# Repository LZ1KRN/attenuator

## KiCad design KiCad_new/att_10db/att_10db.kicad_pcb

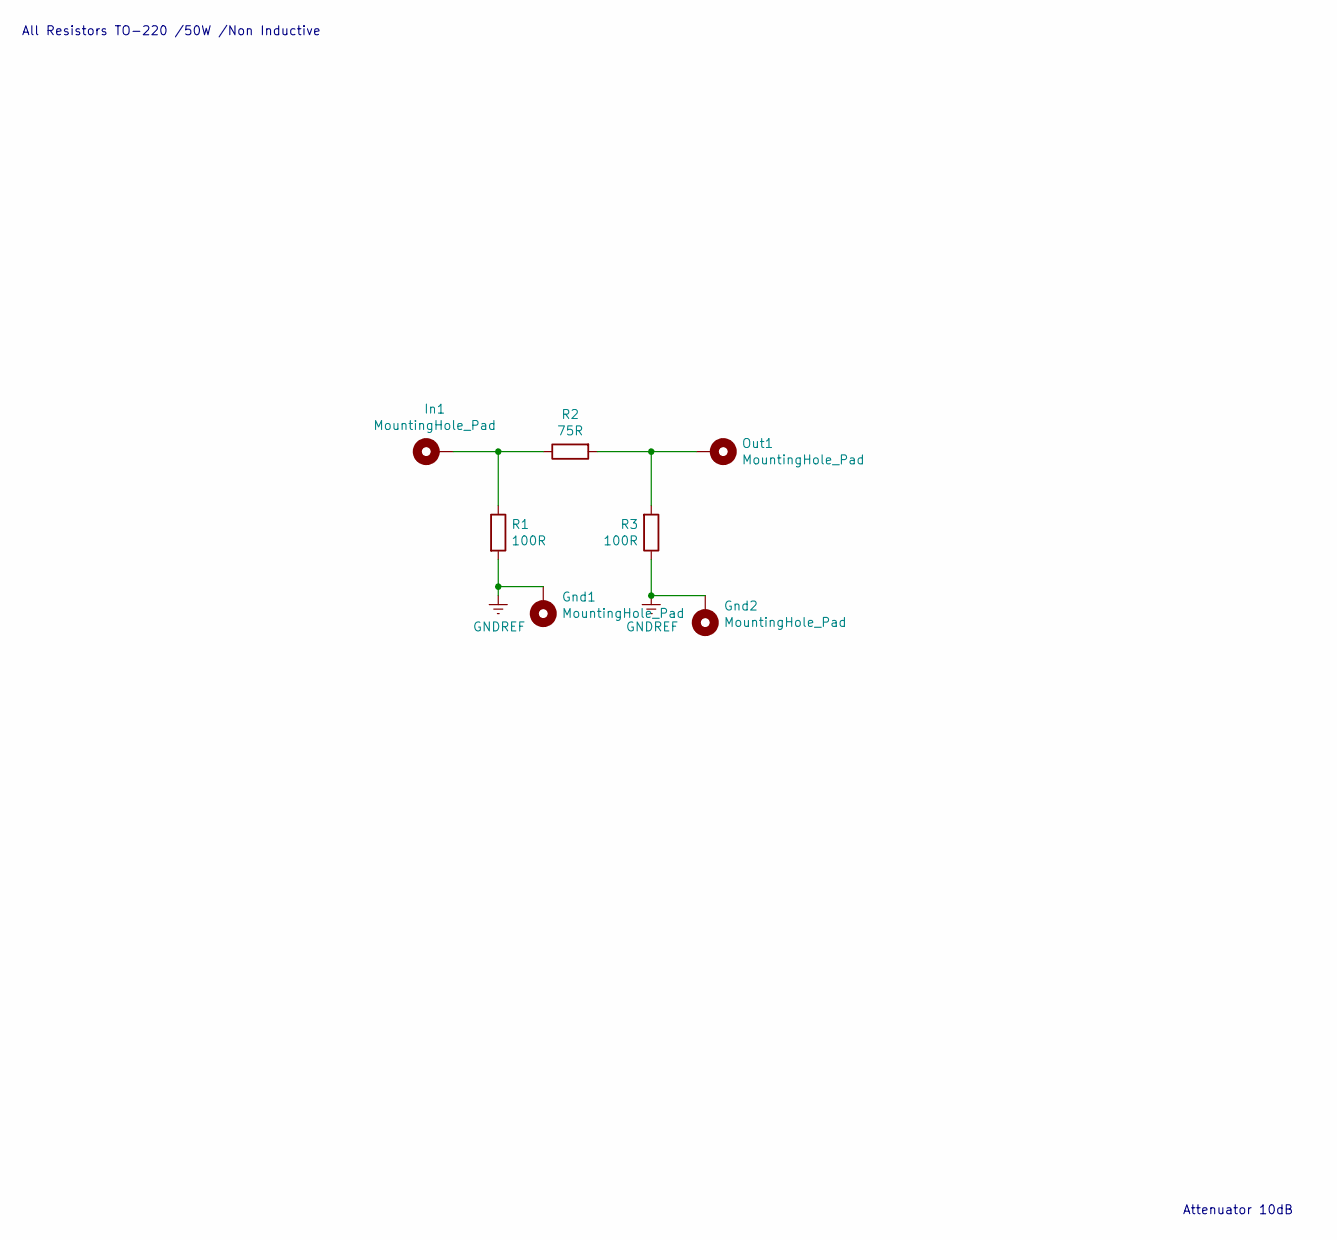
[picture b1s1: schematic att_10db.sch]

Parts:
Gnd1, Gnd2: MountingHole_Pad; TestPoint_Pad_2.5x2.5mm
In1: MountingHole_Pad; TestPoint_Pad_2.5x2.5mm
Out1: MountingHole_Pad; TestPoint_Pad_2.5x2.5mm
R1, R3: 100R; TO-220-2_Horizontal_TabDown
R2: 75R; TO-220-2_Horizontal_TabDown

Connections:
GNDREF: Gnd1.1, Gnd2.1, R1.2, R3.1
unnamed: In1.1, R1.1, R2.1
unnamed: Out1.1, R2.2, R3.2

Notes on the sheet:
Attenuator 10dB
All Resistors TO-220 /50W /Non Inductive

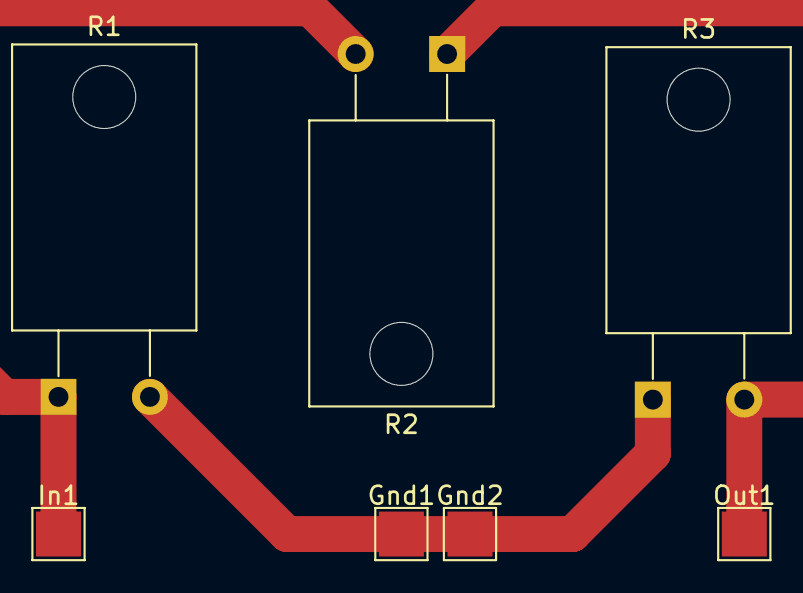
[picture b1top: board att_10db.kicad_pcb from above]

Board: 2 copper layers, 7 parts (0 on the bottom side), 3 nets.

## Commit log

2020-01-19 10db Attenuator Design Board need redesign
2020-01-19 One more GND pad dded
